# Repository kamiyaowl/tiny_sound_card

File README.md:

# tiny_sound_card
名刺サイズのボードでArduino Pro Mini同等のボードで、mp3を再生したりできるモジュール

ドア開閉時の音声再生モジュールや簡易mp3プレイヤーを簡単に制作できます。

## 特徴

* Arduino Pro Miniと同じ開発環境で開発を行え、mp3の音声再生が簡単に行なえます
* スイッチ、mp3再生モジュール、外部スイッチ、SPI、I2Cの準備がしており拡張が容易です
* 表面実装部品が2個のみと、はんだづけの難易度が低いです
* 殆どの部品を秋月電子で購入可能です

## HW仕様

ピン番号 | ボード機能 | ピン機能 | 備考
--------|-------|------|---
D0 | PinHeader | UART RXD | Arduino Bootloader書き込み用
D1 | PinHeader | UART TXD | Arduino Bootloader書き込み用
D2 | LED | Digital Output |
D3 | PinHeader | Digital Input | スイッチ入力用。チャタリング防止回路有
D4 | SW0 | Digital Input | スライドスイッチ
D5 | BTN0 | Digital Input | タクトスイッチ0
D6 | BTN1 | Digital Input | タクトスイッチ1
D7 | BTN2 | Digital Input | タクトスイッチ2
D8 | BTN3 | Digital Input | タクトスイッチ3
D9 | mp3player Control | UART TXD | mp3モジュール制御用
D10 | PinHeader | Digital Output | 外部モジュール接続用SPI
D11 | PinHeader | SPI MOSI | 外部モジュール接続用SPI
D12 | PinHeader | SPI MISO | 外部モジュール接続用SPI
D13 | PinHeader | SPI SCK | 外部モジュール接続用SPI
A0(D14) | mp3player Control | UART RXD | mp3モジュール制御用
A1(D15) | mp3player Control | Digital Input | mp3player再生中にLow
A2(D16) | mp3player Power Control | Digital Output | mp3player電源EN
A3(D17) | mp3player Power Control | Digital Input | mp3player電源/FAULT
A4 | PinHeader | I2C SDA | 外部モジュール接続用I2C
A5 | PinHeader | I2C SCL | 外部モジュール接続用I2C

* スイッチ回路(D3,4,5,6,7,8)にはチャタリング防止回路を実装
* SPI端子はISP(In System Programming)回路も兼用しています
* mp3 playerとはSoftwareSerialを使用して通信を行います
  * [Datasheet](http://akizukidenshi.com/download/ds/dfrobot/DFPlayer_Mini_Manual.pdf)
* mp3 playerモジュールの消費電力が大きいため、ハイサイドスイッチで電源断できるようになっています
  * 不要であれば、U1の1-5pinを短絡してください
   * [Datasheet](https://docs-apac.rs-online.com/webdocs/140d/0900766b8140da8f.pdf)

## SW仕様

準備予定

## 製造ファイル

| ファイルパス | 種別 |
| --- | --- |
`kicad/gerber` | 基盤製造ファイル
`kicad/acrylic_cover/tiny_sound_card-Eco1.User.svg` | 表面アクリルカバー
`kicad/acrylic_cover/tiny_sound_card-Eco2.User.svg` | 裏面アクリルカバー

## 購入部品

| 参照記号                              | 購入先           | 数量 | URL                                                                |
|-----------------------------------|---------------|----|--------------------------------------------------------------------|
| U1                                | RS Components | 1  | https://jp.rs-online.com/web/p/intelligent-power-switches/8805406/ |
| R7,R9,R10,R11,R12,R13             | 秋月            | 1  | http://akizukidenshi.com/catalog/g/gR-25473/                       |
| R2,R3,R6                          | 秋月            | 1  | http://akizukidenshi.com/catalog/g/gR-25103/                       |
| R1,R4                             | 秋月            | 1  | http://akizukidenshi.com/catalog/g/gR-25102/                       |
| CP1                               | 秋月            | 1  | http://akizukidenshi.com/catalog/g/gP-10596/                       |
| SW1,SW5                           | 秋月            | 1  | http://akizukidenshi.com/catalog/g/gP-08789/                       |
| Y1                                | 秋月            | 1  | http://akizukidenshi.com/catalog/g/gP-08671/                       |
| C4,C5                             | 秋月            | 1  | http://akizukidenshi.com/catalog/g/gP-04060/                       |
| SW2,SW3,SW4,SW6                   | 秋月            | 4  | http://akizukidenshi.com/catalog/g/gP-03647/                       |
| F1                                | 秋月            | 1  | http://akizukidenshi.com/catalog/g/gP-00777/                       |
| C1,C2,C3,C6,C7,C9,C10,C11,C12,C13 | 秋月            | 1  | http://akizukidenshi.com/catalog/g/gP-00090/                       |
| M1                                | 秋月            | 1  | http://akizukidenshi.com/catalog/g/gM-12544/                       |
| D1                                | 秋月            | 1  | http://akizukidenshi.com/catalog/g/gI-11578/                       |
| IC1                               | 秋月            | 1  | http://akizukidenshi.com/catalog/g/gI-04386/                       |
| J1                                | 秋月            | 1  | http://akizukidenshi.com/catalog/g/gC-02460/                       |
| P2                                | 秋月            | 1  | http://akizukidenshi.com/catalog/g/gC-01627/                       |
| CON1                              | 秋月            | 1  | http://akizukidenshi.com/catalog/g/gC-00077/                       |

## License

MIT

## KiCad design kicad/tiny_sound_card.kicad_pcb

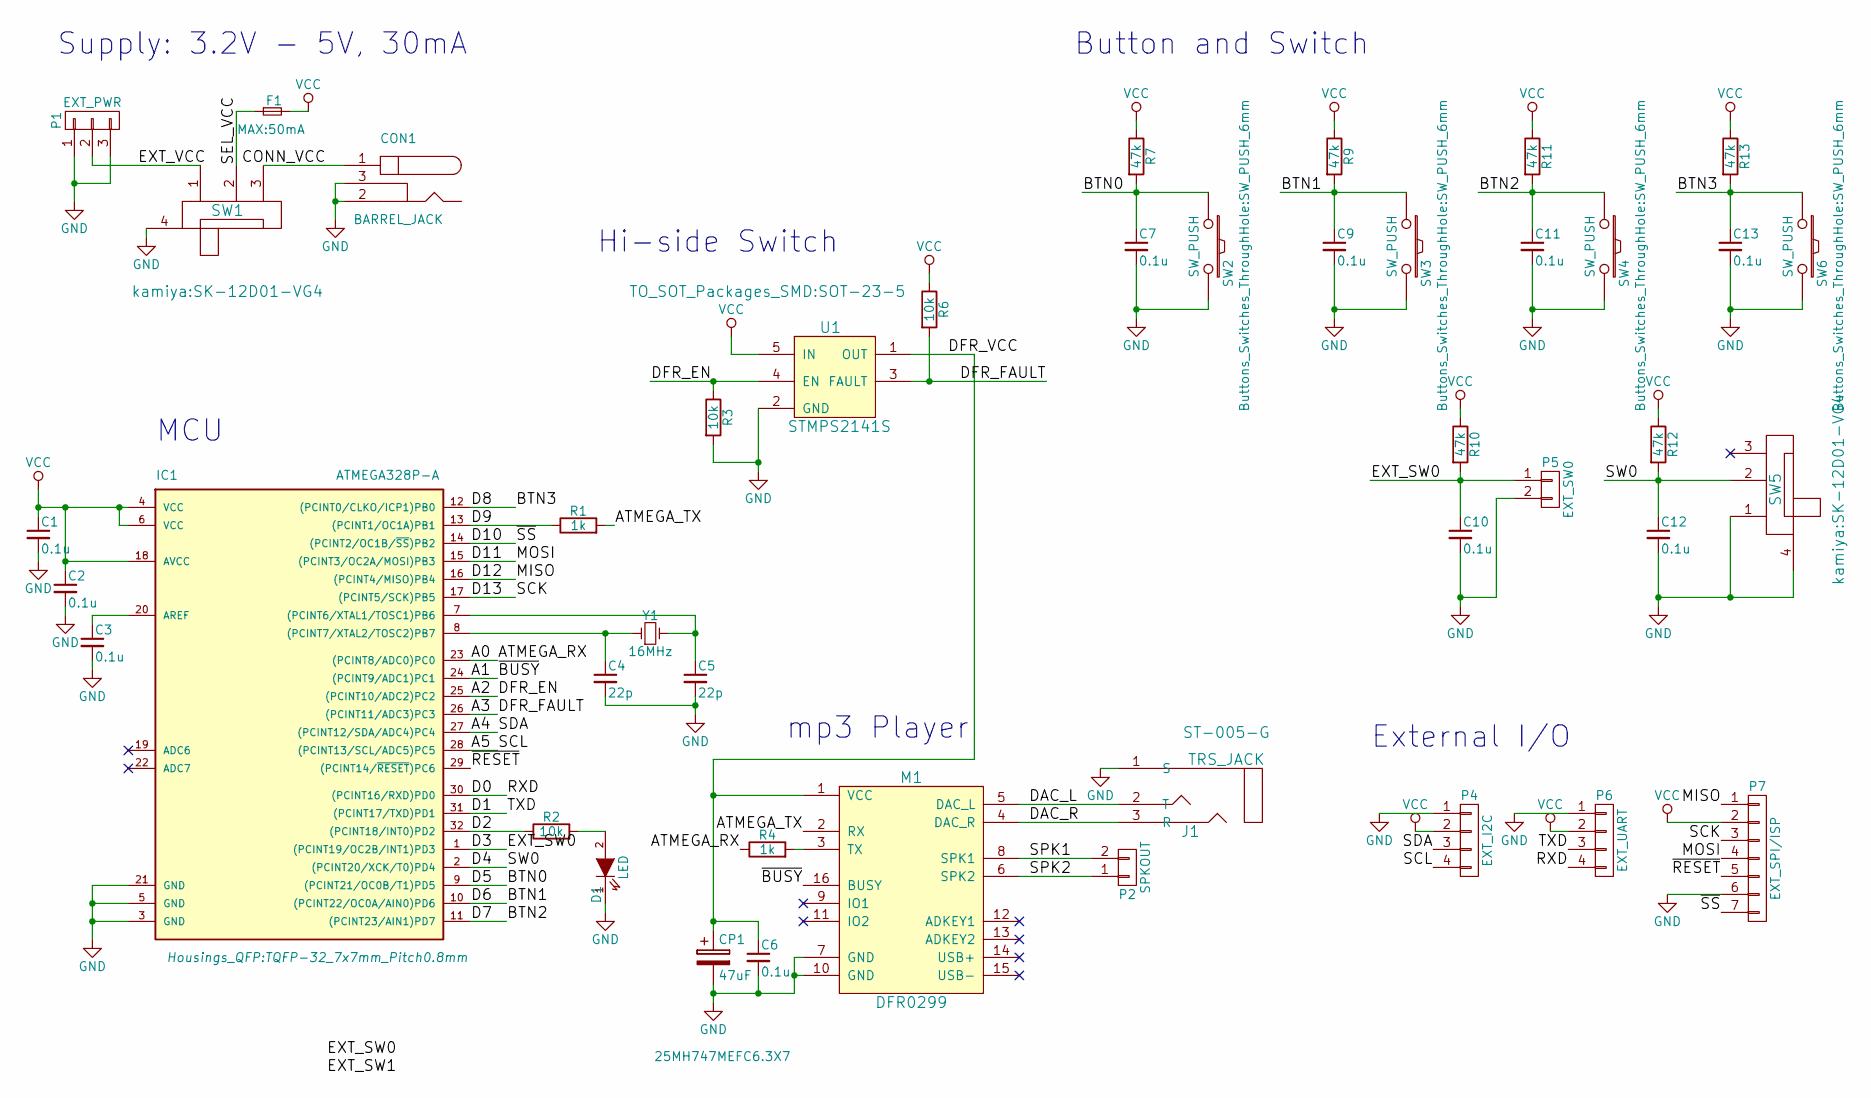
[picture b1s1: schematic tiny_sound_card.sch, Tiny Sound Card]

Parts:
C1, C2, C3, C6, C7, C9, C10, C11, C12, C13: 0.1u; C_Disc_D3.8mm_W2.6mm_P2.50mm
C4, C5: 22p; C_Disc_D3.8mm_W2.6mm_P2.50mm
CON1: BARREL_JACK
CP1: 47uF; CP_Radial_D10.0mm_P2.50mm
D1: LED; LED_D3.0mm
F1: MAX:50mA; C_Rect_L7.0mm_W4.5mm_P5.00mm
IC1: ATMEGA328P-A; TQFP-32_7x7mm_Pitch0.8mm
J1: TRS_JACK; 3.5mm_TRS_Mini
M1: DFR0299
P1: EXT_PWR; Pin_Header_Angled_1x03_Pitch2.54mm
P2: SPKOUT; Pin_Header_Angled_1x02_Pitch2.54mm
P4: EXT_I2C; Pin_Header_Angled_1x04_Pitch2.54mm
P5: EXT_SW0; Pin_Header_Angled_1x02_Pitch2.54mm
P6: EXT_UART; Pin_Header_Angled_1x04_Pitch2.54mm
P7: EXT_SPI/ISP; Pin_Header_Angled_1x07_Pitch2.54mm
R1, R4: 1k; R_Axial_DIN0207_L6.3mm_D2.5mm_P10.16mm_Horizontal
R2, R3, R6: 10k; R_Axial_DIN0207_L6.3mm_D2.5mm_P10.16mm_Horizontal
R7, R9, R10, R11, R12, R13: 47k; R_Axial_DIN0207_L6.3mm_D2.5mm_P10.16mm_Horizontal
SW1, SW5: SlideSW; SK-12D01-VG4
SW2, SW3, SW4, SW6: SW_PUSH; SW_PUSH_6mm
U1: STMPS2141S; SOT-23-5
Y1: 16MHz; Crystal_HC49-4H_Vertical

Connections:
/A0: IC1.23 ((PCINT8/ADC0)PC0), R4.1
/A1: IC1.24 ((PCINT9/ADC1)PC1), M1.16 (BUSY)
/A2: IC1.25 ((PCINT10/ADC2)PC2), R3.1, U1.4 (EN)
/A3: IC1.26 ((PCINT11/ADC3)PC3), R6.2, U1.3 (FAULT)
/A4: IC1.27 ((PCINT12/SDA/ADC4)PC4), P4.3
/A5: IC1.28 ((PCINT13/SCL/ADC5)PC5), P4.4
/ATMEGA_TX: M1.2 (RX), R1.2
/BTN0: C7.1, IC1.9 ((PCINT21/OC0B/T1)PD5), R7.2, SW2.1
/BTN1: C9.1, IC1.10 ((PCINT22/OC0A/AIN0)PD6), R9.2, SW3.1
/BTN2: C11.1, IC1.11 ((PCINT23/AIN1)PD7), R11.2, SW4.1
/BTN3: C13.1, IC1.12 ((PCINT0/CLKO/ICP1)PB0), R13.2, SW6.1
/CONN_VCC: CON1.1, SW1.3
/D0: IC1.30 ((PCINT16/RXD)PD0), P6.4
/D1: IC1.31 ((PCINT17/TXD)PD1), P6.3
/D2: IC1.32 ((PCINT18/INT0)PD2), R2.1
/D3: C10.1, IC1.1 ((PCINT19/OC2B/INT1)PD3), P5.1, R10.2
/D4: C12.1, IC1.2 ((PCINT20/XCK/T0)PD4), R12.2, SW5.2
/D9: IC1.13 ((PCINT1/OC1A)PB1), R1.1
/D10: IC1.14 ((PCINT2/OC1B/~SS~)PB2), P7.7
/D11: IC1.15 ((PCINT3/OC2A/MOSI)PB3), P7.4
/D12: IC1.16 ((PCINT4/MISO)PB4), P7.1
/D13: IC1.17 ((PCINT5/SCK)PB5), P7.3
/DAC_L: J1.2 (T), M1.5 (DAC_L)
/DAC_R: J1.3 (R), M1.4 (DAC_R)
/DFR_VCC: C6.1, CP1.1, M1.1 (VCC), U1.1 (OUT)
/EXT_VCC: P1.2, SW1.1
/SEL_VCC: F1.1, SW1.2
/SPK1: M1.8 (SPK1), P2.2
/SPK2: M1.6 (SPK2), P2.1
/~RESET: IC1.29 ((PCINT14/~RESET~)PC6), P7.5
GND: C1.2, C2.2, C3.2, C4.2, C5.2, C6.2, C7.2, C9.2, C10.2, C11.2, C12.2, C13.2, CON1.2, CON1.3, CP1.2, D1.1 (K), IC1.3 (GND), IC1.5 (GND), IC1.21 (GND), J1.1 (S), M1.7 (GND), M1.10 (GND), P1.1, P1.3, P4.1, P5.2, P6.1, P7.6, R3.2, SW1.4, SW2.2, SW3.2, SW4.2, SW5.1, SW5.4, SW6.2, U1.2 (GND)
unnamed: C3.1, IC1.20 (AREF)
unnamed: C4.1, IC1.8 ((PCINT7/XTAL2/TOSC2)PB7), Y1.1
unnamed: C5.1, IC1.7 ((PCINT6/XTAL1/TOSC1)PB6), Y1.2
unnamed: D1.2 (A), R2.2
unnamed: M1.3 (TX), R4.2
VCC: C1.1, C2.1, F1.2, IC1.4 (VCC), IC1.6 (VCC), IC1.18 (AVCC), P4.2, P6.2, P7.2, R6.1, R7.1, R9.1, R10.1, R11.1, R12.1, R13.1, U1.5 (IN)

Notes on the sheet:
Supply: 3.2V - 5V, 30mA
Button and Switch
MCU
Hi-side Switch
mp3 Player
External I/O

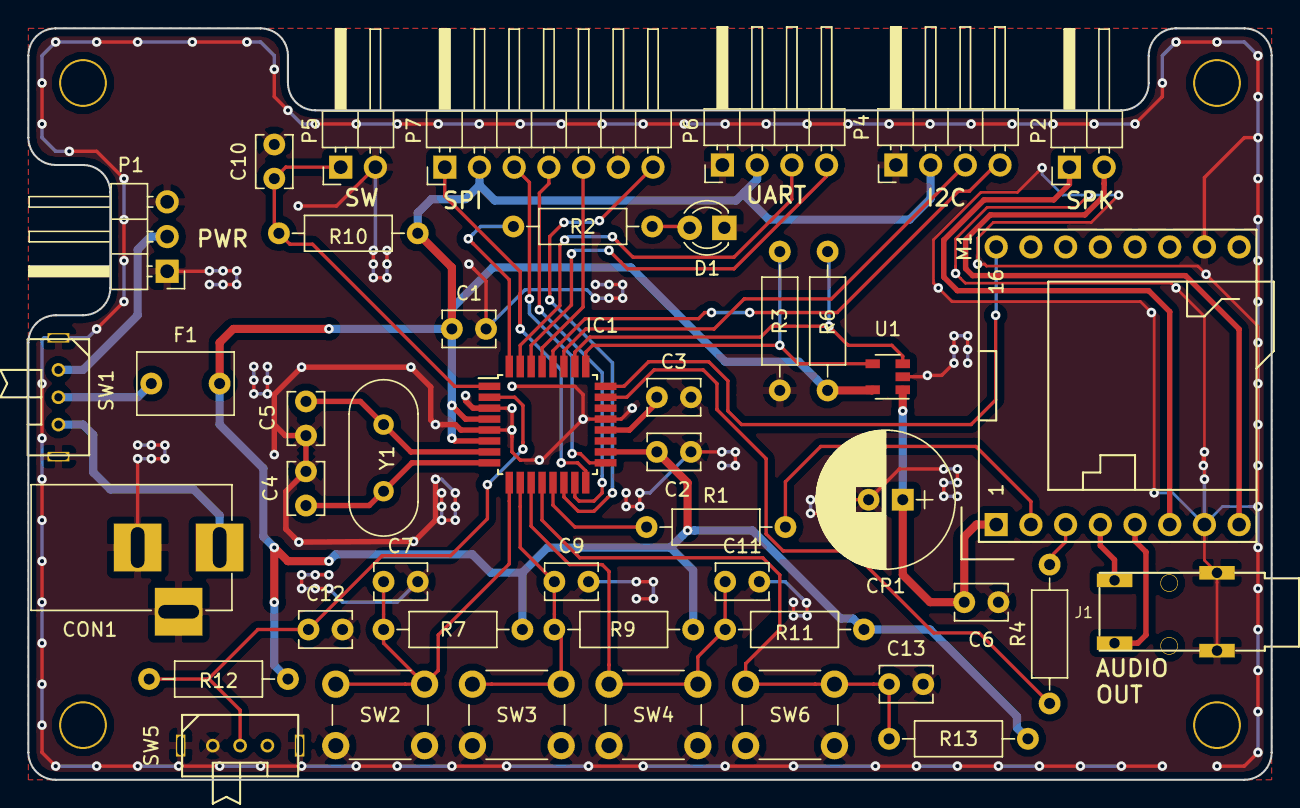
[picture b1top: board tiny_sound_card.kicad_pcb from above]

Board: 2 copper layers, 91.0 x 55.0 mm, 48 parts (0 on the bottom side), 37 nets.

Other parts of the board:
P4#2, P8, P9, P10: M3Drill; M3Drill2

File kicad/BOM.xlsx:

ID | 参照記号 | パッケージ | 数 | 名称 | 購入先コウニュウサキ | 数量スウリョウ | URL
15 | U1 | SOT-23-5 | 1 | STMPS2141S | RS Components | 1 | https://jp.rs-online.com/web/p/intelligent-power-switches/8805406/
13 | R7,R9,R10,R11,R12,R13 | R_Axial_DIN0207_L6.3mm_D2.5mm_P10.16mm_Horizontal | 6 | 47k | 秋月アキヅキ | 1 | http://akizukidenshi.com/catalog/g/gR-25473/
12 | R2,R3,R6 | R_Axial_DIN0207_L6.3mm_D2.5mm_P10.16mm_Horizontal | 3 | 10k | 秋月アキヅキ | 1 | http://akizukidenshi.com/catalog/g/gR-25103/
23 | R1,R4 | R_Axial_DIN0207_L6.3mm_D2.5mm_P10.16mm_Horizontal | 2 | 1k | 秋月アキヅキ | 1 | http://akizukidenshi.com/catalog/g/gR-25102/
21 | CP1 | CP_Radial_D10.0mm_P2.50mm | 1 | 47uF | 秋月アキヅキ | 1 | http://akizukidenshi.com/catalog/g/gP-10596/
14 | SW1,SW5 | SK-12D01-VG4 | 2 | SlideSW | 秋月アキヅキ | 1 | http://akizukidenshi.com/catalog/g/gP-08789/
16 | Y1 | Crystal_HC49-4H_Vertical | 1 | 16MHz | 秋月アキヅキ | 1 | http://akizukidenshi.com/catalog/g/gP-08671/
3 | C4,C5 | C_Disc_D3.8mm_W2.6mm_P2.50mm | 2 | 22p | 秋月アキヅキ | 1 | http://akizukidenshi.com/catalog/g/gP-04060/
22 | SW2,SW3,SW4,SW6 | SW_PUSH_6mm | 4 | SW_PUSH | 秋月アキヅキ | 4 | http://akizukidenshi.com/catalog/g/gP-03647/
6 | F1 | C_Rect_L7.0mm_W4.5mm_P5.00mm | 1 | MAX:50mA | 秋月アキヅキ | 1 | http://akizukidenshi.com/catalog/g/gP-00777/
2 | C1,C2,C3,C6,C7,C9,C10,C11,C12,C13 | C_Disc_D3.8mm_W2.6mm_P2.50mm | 10 | 0.1u | 秋月アキヅキ | 1 | http://akizukidenshi.com/catalog/g/gP-00090/
17 | M1 | DFR0299 | 1 | DFR0299 | 秋月アキヅキ | 1 | http://akizukidenshi.com/catalog/g/gM-12544/
5 | D1 | LED_D3.0mm | 1 | LED | 秋月アキヅキ | 1 | http://akizukidenshi.com/catalog/g/gI-11578/
7 | IC1 | TQFP-32_7x7mm_Pitch0.8mm | 1 | ATMEGA328P-A | 秋月アキヅキ | 1 | http://akizukidenshi.com/catalog/g/gI-04386/
8 | J1 | 3.5mm_TRS_Mini | 1 | TRS_JACK | 秋月アキヅキ | 1 | http://akizukidenshi.com/catalog/g/gC-02460/
10 | P2 | Pin_Header_Angled_1x02_Pitch2.54mm | 1 | SPKOUT | 秋月アキヅキ | 1 | http://akizukidenshi.com/catalog/g/gC-01627/
4 | CON1 | BARREL_JACK | 1 | BARREL_JACK | 秋月アキヅキ | 1 | http://akizukidenshi.com/catalog/g/gC-00077/
24 | G*** | logo-silk | 1 | LOGO
1 | P10,P9,P8,P4 | M3Drill2 | 4 | M3Drill
11 | P5 | Pin_Header_Angled_1x02_Pitch2.54mm | 1 | EXT_SW0
9 | P1 | Pin_Header_Angled_1x03_Pitch2.54mm | 1 | EXT_PWR
18 | P4 | Pin_Header_Angled_1x04_Pitch2.54mm | 1 | EXT_I2C
19 | P6 | Pin_Header_Angled_1x04_Pitch2.54mm | 1 | EXT_UART
20 | P7 | Pin_Header_Angled_1x07_Pitch2.54mm | 1 | EXT_SPI/ISP

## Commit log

2018-08-19 回路図を作成
2018-08-19 部品割当の修正と、配置を完了
2018-08-19 デザインルールを設定
2018-08-19 GPIOのアサインを大幅に調整
2018-08-19 基本配線終わり
2018-08-19 外形とパネル表裏を作成
2018-08-20 LEDのポートを変更
2018-08-20 EXT_SW1を削除
2018-08-20 ベタ配線
2018-08-20 シルク位置修正
2018-09-01 Close #1
2018-09-01 ロゴ追加
2018-09-01 シルクでピンアサイン記述を追加
2018-09-01 Update README.md
    HW使用に関して追記
2018-09-01 gerber,acrylicの製造ファイルを作成
2018-09-01 BOM作成、READMEに反映
